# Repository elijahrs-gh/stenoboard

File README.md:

# Stenoboard V1
A 28 key stenography keyboard.

**Finished 3D Render:**

## Pictures

**PCB:**

**Schematic:**

**Case:**

## BOM
| Reference                                                                 | Qty | Value    | DNP | Exclude from BOM | Exclude from Board | Footprint                                                         | Datasheet                                                                                  |
|---------------------------------------------------------------------------|-----|----------|-----|------------------|-------------------|-------------------------------------------------------------------|--------------------------------------------------------------------------------------------|
| A1                                                                        | 1   | RaspberryPi_Pico |     |                  |                   | Module:RaspberryPi_Pico_Common_Unspecified                        | https://datasheets.raspberrypi.com/pico/pico-datasheet.pdf                                 |
| D1, D2                                                                    | 2   | SK6812MINI |     |                  |                   | LED_SMD:LED_SK6812MINI_PLCC4_3.5x3.5mm_P1.75mm                    | https://cdn-shop.adafruit.com/product-files/2686/SK6812MINI_REV.01-1-2.pdf                 |
| D3–D30 (28 parts)                                                         | 28  | 1N4148   |     |                  |                   | Diode_THT:D_DO-35_SOD27_P7.62mm_Horizontal                        | https://assets.nexperia.com/documents/data-sheet/1N4148_1N4448.pdf                         |
| SW1–SW28 (28 switches)                                                    | 28  | SW_Push  |     |                  |                   | Button_Switch_Keyboard:SW_Cherry_MX_1.00u_PCB                     | ~                                                                                            |

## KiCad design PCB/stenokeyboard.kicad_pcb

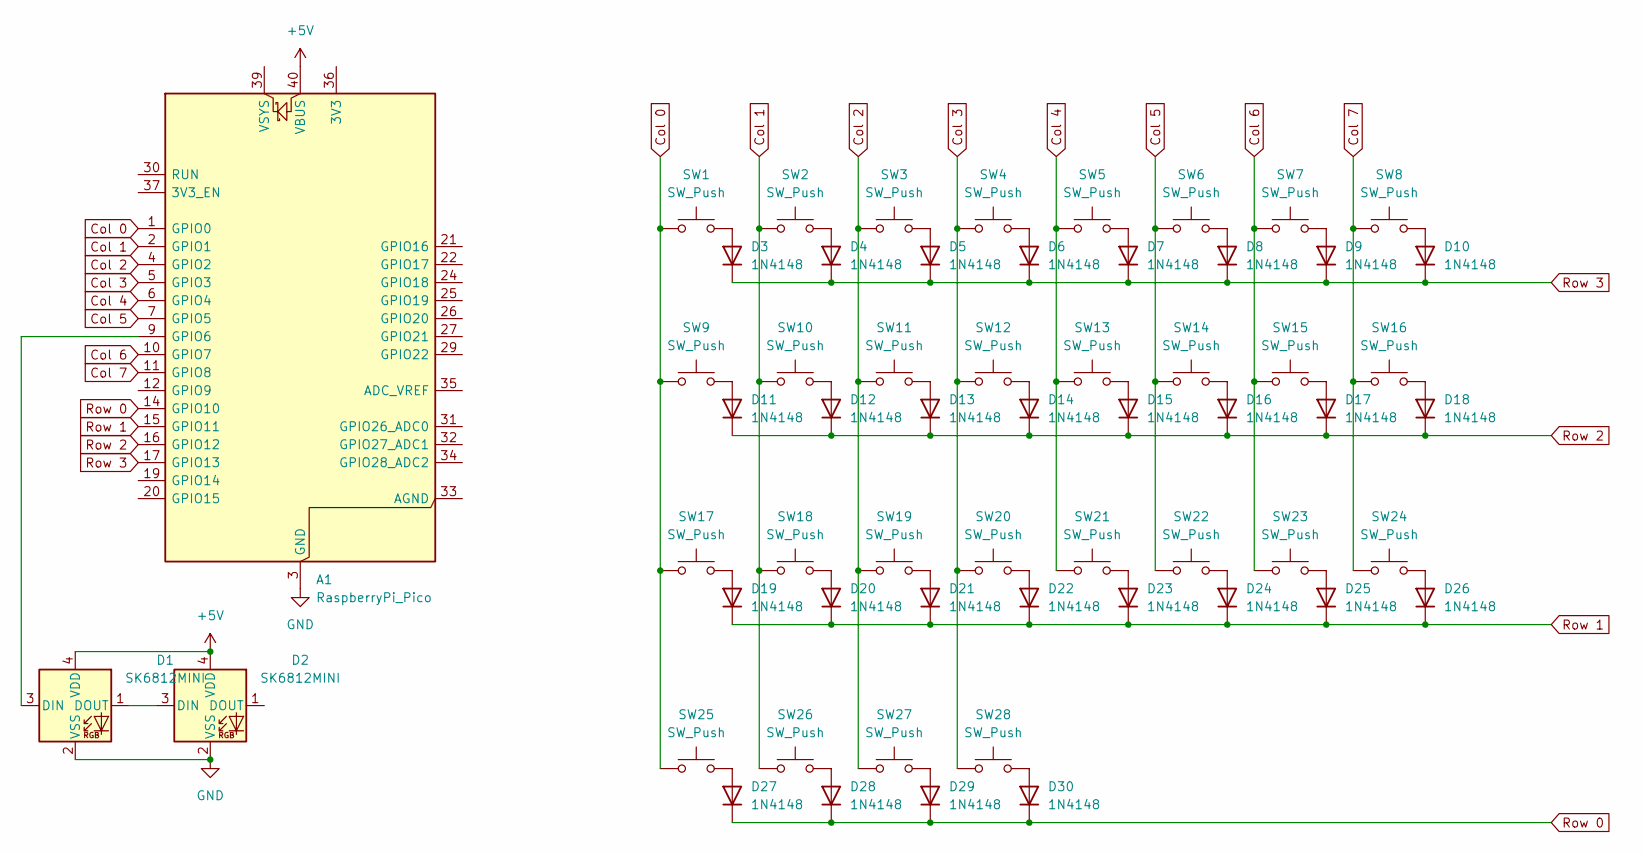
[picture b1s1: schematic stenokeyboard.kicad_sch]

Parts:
A1: RaspberryPi_Pico; RaspberryPi_Pico_Common_Unspecified
D1, D2: SK6812MINI; LED_SK6812MINI_PLCC4_3.5x3.5mm_P1.75mm
D3, D4, D5, D6, D7, D8, D9, D10, D11, D12, D13, D14, D15, D16, D17, D18, D19, D20, D21, D22, D23, D24, D25, D26, D27, D28, D29, D30: 1N4148; D_DO-35_SOD27_P7.62mm_Horizontal
SW1, SW2, SW3, SW4, SW5, SW6, SW7, SW8, SW9, SW10, SW11, SW12, SW13, SW14, SW15, SW16, SW17, SW18, SW19, SW20, SW21, SW22, SW23, SW24, SW25, SW26, SW27, SW28: SW_Push; SW_Cherry_MX_1.00u_PCB

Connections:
+5V: A1.40 (VBUS), D1.4 (VDD), D2.4 (VDD)
Col 0: A1.1 (GPIO0), SW1.1, SW9.1, SW17.1, SW25.1
Col 1: A1.2 (GPIO1), SW2.1, SW10.1, SW18.1, SW26.1
Col 2: A1.4 (GPIO2), SW3.1, SW11.1, SW19.1, SW27.1
Col 3: A1.5 (GPIO3), SW4.1, SW12.1, SW20.1, SW28.1
Col 4: A1.6 (GPIO4), SW5.1, SW13.1, SW21.1
Col 5: A1.7 (GPIO5), SW6.1, SW14.1, SW22.1
Col 6: A1.10 (GPIO7), SW7.1, SW15.1, SW23.1
Col 7: A1.11 (GPIO8), SW8.1, SW16.1, SW24.1
GND: A1.3 (GND), A1.8 (GND), A1.13 (GND), A1.18 (GND), A1.23 (GND), A1.28 (GND), A1.38 (GND), D1.2 (VSS), D2.2 (VSS)
unnamed: A1.9 (GPIO6), D1.3 (DIN)
unnamed: D1.1 (DOUT), D2.3 (DIN)
unnamed: D3.2 (A), SW1.2
unnamed: D4.2 (A), SW2.2
unnamed: D5.2 (A), SW3.2
unnamed: D6.2 (A), SW4.2
unnamed: D7.2 (A), SW5.2
unnamed: D8.2 (A), SW6.2
unnamed: D9.2 (A), SW7.2
unnamed: D10.2 (A), SW8.2
unnamed: D11.2 (A), SW9.2
unnamed: D12.2 (A), SW10.2
unnamed: D13.2 (A), SW11.2
unnamed: D14.2 (A), SW12.2
unnamed: D15.2 (A), SW13.2
unnamed: D16.2 (A), SW14.2
unnamed: D17.2 (A), SW15.2
unnamed: D18.2 (A), SW16.2
unnamed: D19.2 (A), SW17.2
unnamed: D20.2 (A), SW18.2
unnamed: D21.2 (A), SW19.2
unnamed: D22.2 (A), SW20.2
unnamed: D23.2 (A), SW21.2
unnamed: D24.2 (A), SW22.2
unnamed: D25.2 (A), SW23.2
unnamed: D26.2 (A), SW24.2
unnamed: D27.2 (A), SW25.2
unnamed: D28.2 (A), SW26.2
unnamed: D29.2 (A), SW27.2
unnamed: D30.2 (A), SW28.2
Row 0: A1.14 (GPIO10), D27.1 (K), D28.1 (K), D29.1 (K), D30.1 (K)
Row 1: A1.15 (GPIO11), D19.1 (K), D20.1 (K), D21.1 (K), D22.1 (K), D23.1 (K), D24.1 (K), D25.1 (K), D26.1 (K)
Row 2: A1.16 (GPIO12), D11.1 (K), D12.1 (K), D13.1 (K), D14.1 (K), D15.1 (K), D16.1 (K), D17.1 (K), D18.1 (K)
Row 3: A1.17 (GPIO13), D3.1 (K), D4.1 (K), D5.1 (K), D6.1 (K), D7.1 (K), D8.1 (K), D9.1 (K), D10.1 (K)

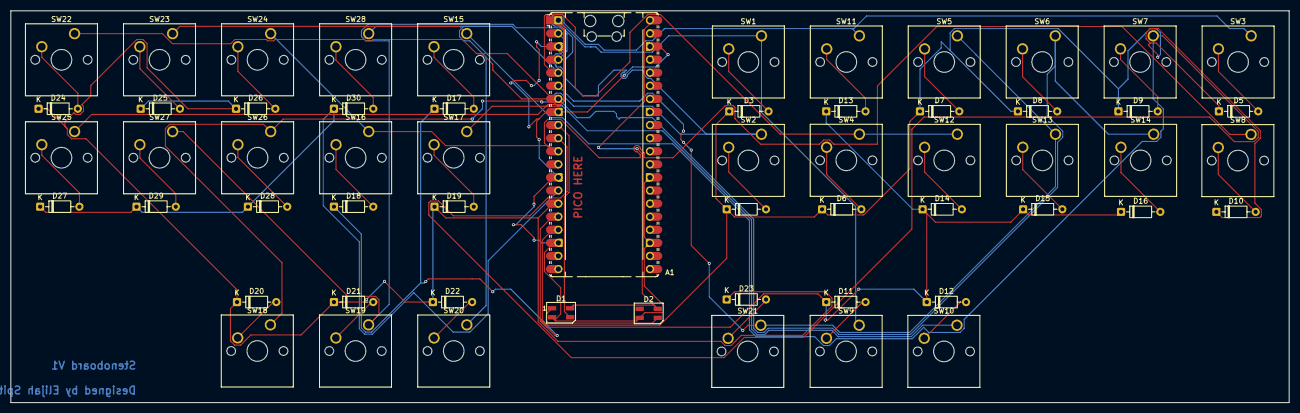
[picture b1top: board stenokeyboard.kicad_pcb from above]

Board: 2 copper layers, 248.0 x 76.0 mm, 59 parts (0 on the bottom side), 44 nets.
